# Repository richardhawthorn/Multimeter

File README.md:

### Features

- 4 character 7-segment LED display
- ATMEGA328P with Arduino boot-loader
- 5V operation @ 16Mhz
- Voltage and current measurement
- USB-A socket for current passthrough measurement
- 1x button to cycle through modes
- Mini USB power connector
- FTDI programming port
- ICSP port

### License

This work is licensed under a Creative Commons Attribution-ShareAlike 4.0 International License.

<br />
Designed by <a xmlns:cc="http://creativecommons.org/ns#" href="http://www.richardhawthorn.com" property="cc:attributionName" rel="cc:attributionURL" target="_blank">Richard Hawthorn</a><br />
<a rel="license" href="http://creativecommons.org/licenses/by-sa/4.0/" target="_blank">View License</a>

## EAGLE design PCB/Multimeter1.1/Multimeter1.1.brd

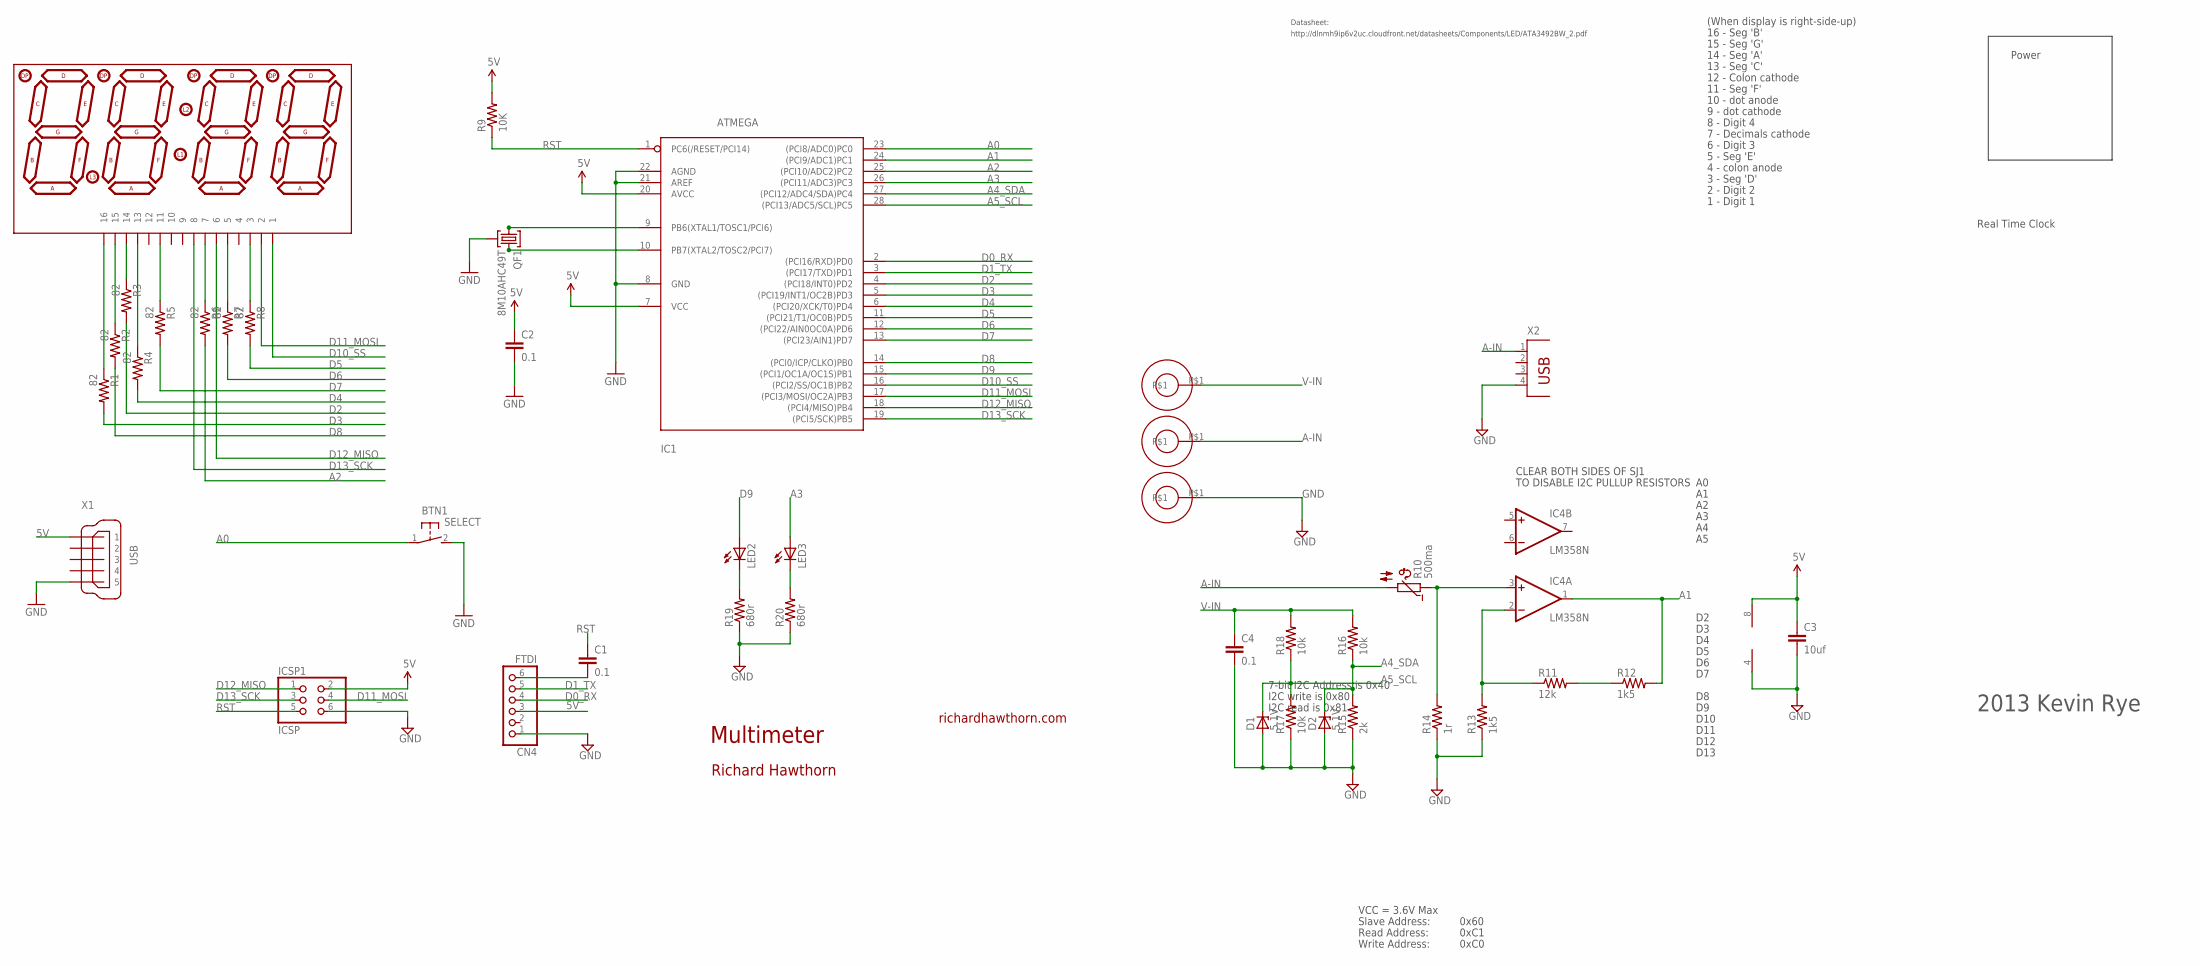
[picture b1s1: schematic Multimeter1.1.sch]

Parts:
BTN1: SELECT; DTS-3
C1, C2, C4: 0.1; CAP-PTH-SMALL2
C3: 10uf; CAP-PTH-SMALL2
CN4: FTDI; 1X06
D1, D2: 5.1V; DO34Z7
IC1: ATMEGA; DIL28-3-ROUND
IC4: LM358N; DIL08
ICSP1: ICSP; 2X03
LED1: 7SEG-4DIGIT; SPARKFUN_7-SEGMENT-4DIGIT
LED2, LED3: LED5MM
QF1: 8M10AHC49T; HC49U
R1, R2, R3, R4, R5, R6, R7, R8: 82; 0204/7
R9: 10K; 0204/7
R10: 500ma; B57164
R11: 12k; 0204/7
R12, R13: 1k5; 0204/7
R14: 1r; 0204/7
R15: 2k; 0204/7
R16, R17, R18: 10k; 0204/7
R19, R20: 680r; 0204/7
U$1, U$5, U$6: BANANA
X1: USB; 32005-601
X2: PN87520

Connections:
5V: C2.1, C3.1, CN4.3, IC1.7 (VCC), IC1.20 (AVCC), IC4.8 (V+), ICSP1.2, R9.2, X1.1
A0: BTN1.1, IC1.23 ((PCI8/ADC0)PC0)
A1: IC1.24 ((PCI9/ADC1)PC1), IC4.1 (OUT), R12.2
A2: IC1.25 ((PCI10/ADC2)PC2), R6.2
A3: IC1.26 ((PCI11/ADC3)PC3), LED3.A
A4_SDA: D2.C, IC1.27 ((PCI12/ADC4/SDA)PC4), R15.2, R16.1
A5_SCL: D1.C, IC1.28 ((PCI13/ADC5/SCL)PC5), R17.2, R18.1
A-IN: R10.2, U$5.P$1, X2.1
D0_RX: CN4.4, IC1.2 ((PCI16/RXD)PD0)
D1_TX: CN4.5, IC1.3 ((PCI17/TXD)PD1)
D2: IC1.4 ((PCI18/INT0)PD2), R3.2
D3: IC1.5 ((PCI19/INT1/OC2B)PD3), R1.2
D4: IC1.6 ((PCI20/XCK/T0)PD4), R4.2
D5: IC1.11 ((PCI21/T1/OC0B)PD5), R8.2
D6: IC1.12 ((PCI22/AIN0OC0A)PD6), R7.2
D7: IC1.13 ((PCI23/AIN1)PD7), R5.2
D8: IC1.14 ((PCI0/ICP/CLKO)PB0), R2.2
D9: IC1.15 ((PCI1/OC1A/OC1S)PB1), LED2.A
D10_SS: IC1.16 ((PCI2/SS/OC1B)PB2), LED1.1
D11_MOSI: IC1.17 ((PCI3/MOSI/OC2A)PB3), ICSP1.4, LED1.2
D12_MISO: IC1.18 ((PCI4/MISO)PB4), ICSP1.1, LED1.6
D13_SCK: IC1.19 ((PCI5/SCK)PB5), ICSP1.3, LED1.8
GND: BTN1.2, C2.2, C3.2, C4.2, CN4.1, D1.A, D2.A, IC1.8 (GND), IC1.21 (AREF), IC1.22 (AGND), IC4.4 (V-), ICSP1.6, QF1.2, R13.1, R14.1, R15.1, R17.1, R19.1, R20.1, U$6.P$1, X1.5, X2.4
unnamed: LED1.16, R1.1
unnamed: IC4.2 (-IN), R11.1, R13.2
unnamed: LED1.15, R2.1
unnamed: LED2.K (C), R19.2
unnamed: LED3.K (C), R20.2
unnamed: R11.2, R12.1
unnamed: LED1.7, R6.1
unnamed: IC4.3 (+IN), R10.1, R14.2
unnamed: IC1.9 (PB6(XTAL1/TOSC1/PCI6)), QF1.1
unnamed: C1.2, CN4.6
unnamed: LED1.13, R4.1
unnamed: LED1.14, R3.1
unnamed: LED1.11, R5.1
unnamed: IC1.10 (PB7(XTAL2/TOSC2/PCI7)), QF1.3
unnamed: LED1.5, R7.1
unnamed: LED1.3, R8.1
RST: C1.1, IC1.1 (PC6(/RESET/PCI14)), ICSP1.5, R9.1
V-IN: C4.1, R16.2, R18.2, U$1.P$1

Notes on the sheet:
Multimeter
richardhawthorn.com
Richard Hawthorn
CLEAR BOTH SIDES OF SJ1
TO DISABLE I2C PULLUP RESISTORS
7-bit I2C Address is 0x40
I2C write is 0x80
I2C read is 0x81
VCC = 3.6V Max
Read Address:
Write Address:
Slave Address:
0x60
0xC1
0xC0
14 - Seg 'A'
13 - Seg 'C'
12 - Colon cathode
11 - Seg 'F'
10 - dot anode
9 - dot cathode
8 - Digit 4
7 - Decimals cathode
6 - Digit 3
5 - Seg 'E'
4 - colon anode
3 - Seg 'D'
2 - Digit 2
Real Time Clock
1 - Digit 1
15 - Seg 'G'
16 - Seg 'B'
D10
D11
D12
D13
http://dlnmh9ip6v2uc.cloudfront.net/datasheets/Components/LED/ATA3492BW_2.pdf
Datasheet:
Power
(When display is right-side-up)

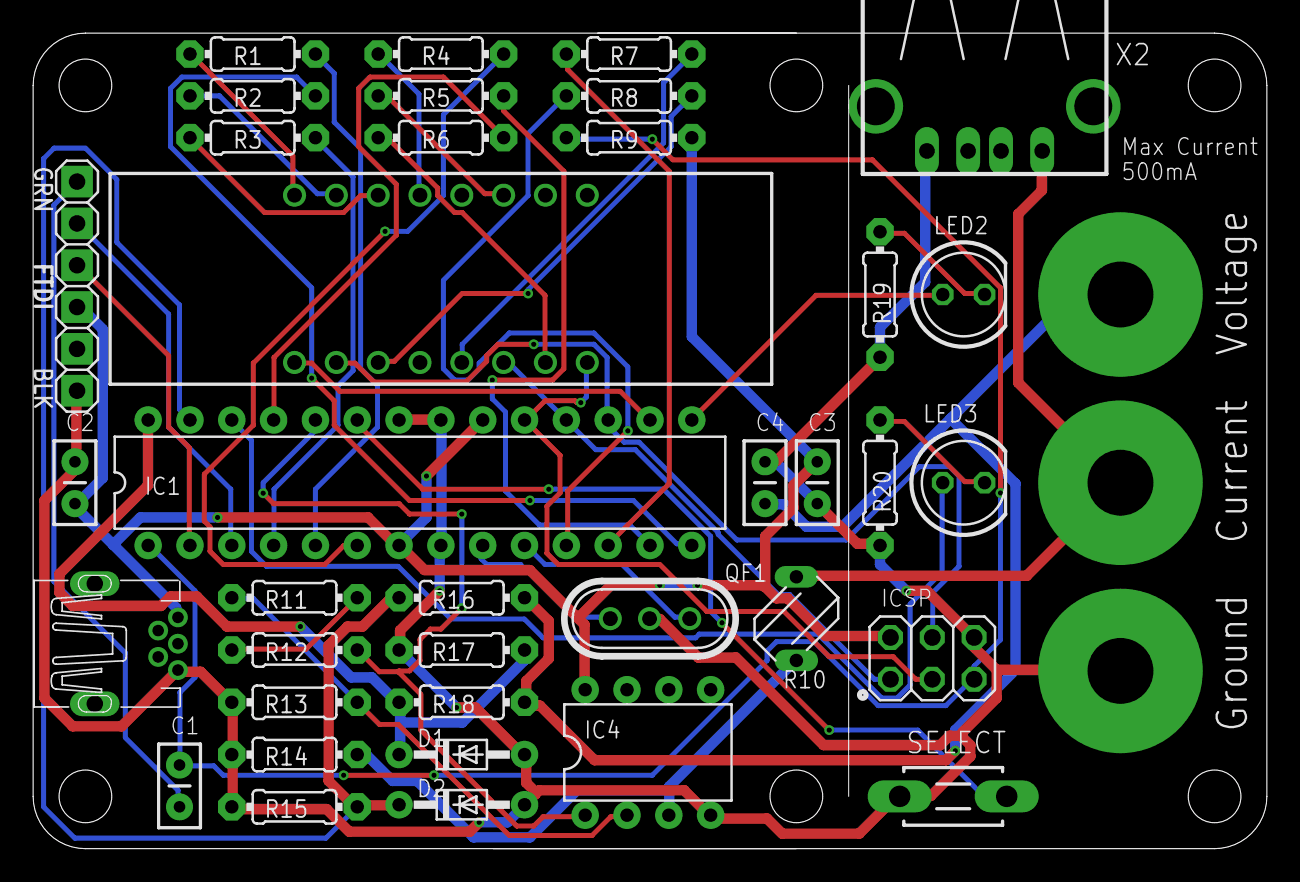
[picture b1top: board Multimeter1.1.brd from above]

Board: 2 copper layers, 74.9 x 49.5 mm, 41 parts (1 on the bottom side), 41 nets.

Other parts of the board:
U$3: OSHW-LOGO-S

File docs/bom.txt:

Partlist exported from /Users/richard/Projects/Multimeter/PCB/Multimeter1.2/Multimeter1.2.sch at 7/30/15 9:30 PM

Qty Value       Device                       Package                   Parts                          Description                      
1               PN87520                      PN87520                   USB2                           BERG USB connector               
3   0.1         CAPPTH2                      CAP-PTH-SMALL2            C1, C2, C4                     Capacitor                        
1   10K         R-US_0204/7                  0204/7                    R9                             RESISTOR, American symbol        
3   10k         R-US_0204/7                  0204/7                    R16, R17, R18                  RESISTOR, American symbol        
1   10uf        CAPPTH2                      CAP-PTH-SMALL2            C3                             Capacitor                        
1   12k         R-US_0204/7                  0204/7                    R11                            RESISTOR, American symbol        
2   1k5         R-US_0204/7                  0204/7                    R12, R13                       RESISTOR, American symbol        
1   1r          R-US_0204/7                  0204/7                    R14                            RESISTOR, American symbol        
1   2k          R-US_0204/7                  0204/7                    R15                            RESISTOR, American symbol        
2   5.1V        BZX90                        DO34Z7                    D1, D2                         Z DIODE                          
1   500mA       B57164                       B57164                    R10                            SIEMENS NTC                      
1   7SEG-4DIGIT 7SEG-4DIGIT                  SPARKFUN_7-SEGMENT-4DIGIT LED1                                                            
8   82          R-US_0204/7                  0204/7                    R1, R2, R3, R4, R5, R6, R7, R8 RESISTOR, American symbol        
1   8M10AHC49T  8M10AHC49T                   HC49U                     QF1                            Monolithic Crystal Filters       
1   ATMEGA      ATMEGA168PROUND              DIL28-3-ROUND             IC1                            MICROCONTROLLER                  
3   BANANA      BANANA                       BANANA                    U$1, U$5, U$6                                                   
1   F/QMBIII    F/QMBIII                     F/QMBIII                  BZ1                            BUZZER Source: Buerklin          
1   F/TMB       F/TMB                        F/TMB                     BZ2                            BUZZER Source: Buerklin          
1   FTDI        PINHD-1X6                    1X06                      CN4                            PIN HEADER                       
1   ICSP        PINHD-2X3                    2X03                      ICSP1                          PIN HEADER                       
1   LM358N      LM358N                       DIL08                     IC4                            OP AMP also LM158; LM258; LM2904 
1   SELECT      DTS-3                        DTS-3                     BTN1                                                            
1   USB         MINI-USB_SHIELD5P2-32005-601 32005-601                 X1                             MINI USB-B R/A DIP 5pol.

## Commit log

2016-01-06 Adding v1 and v2 pcb designs
2016-01-06 adding pcb images
2016-01-06 adding base drawings
2016-01-06 first version of the Arduino code
2016-01-06 added photo

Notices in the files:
parts and their libraries:
SparkFun-Aesthetics: Licensing: CC v3.0 Share-Alike You are welcome to use this library for commercial purposes.
